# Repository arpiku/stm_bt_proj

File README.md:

# stm_bt_proj
A simple bluetoth PCB project based STM32 Microcontroller.

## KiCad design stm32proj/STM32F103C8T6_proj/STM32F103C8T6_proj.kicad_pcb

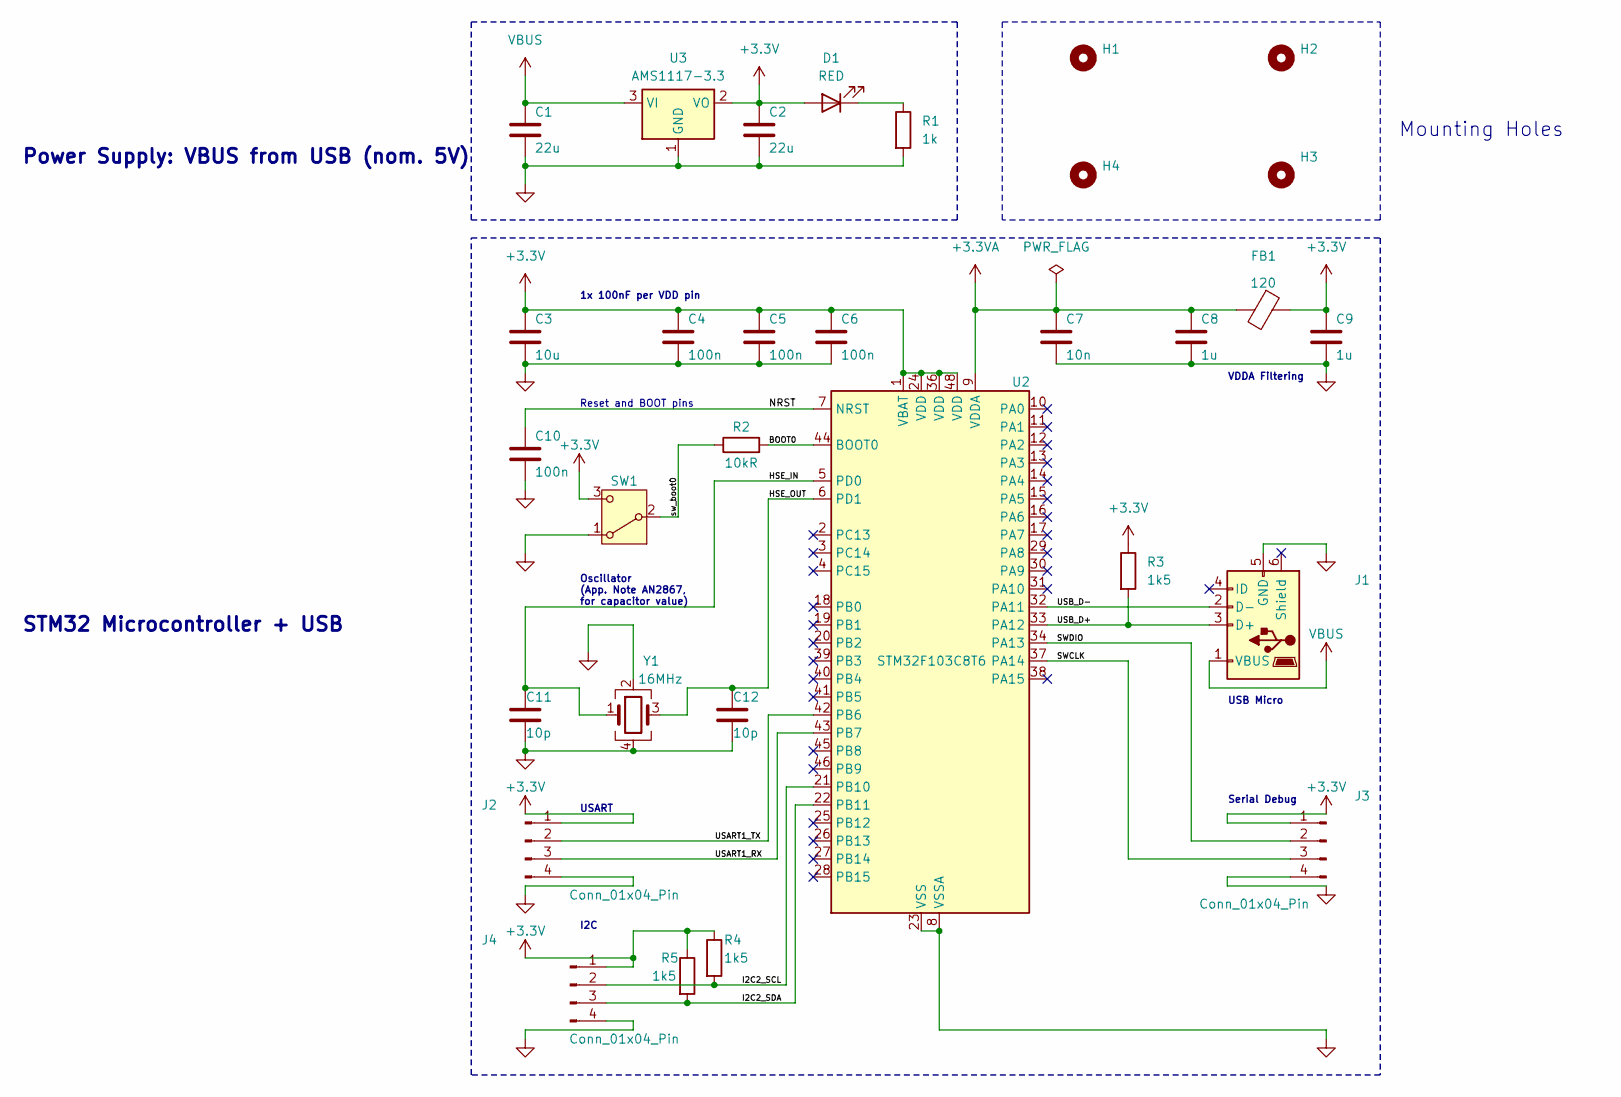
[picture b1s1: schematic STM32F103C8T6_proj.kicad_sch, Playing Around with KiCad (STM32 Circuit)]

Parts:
C1, C2: 22u; C_0805_2012Metric
C3: 10u; C_0805_2012Metric
C4, C5, C6, C10: 100n; C_0402_1005Metric
C7: 10n; C_0402_1005Metric
C8, C9: 1u; C_0402_1005Metric
C11, C12: 10p; C_0402_1005Metric
D1: RED; LED_0402_1005Metric
FB1: 120; L_0603_1608Metric
H1, H2, H3, H4: MountingHole; MountingHole_2.2mm_M2
J1: USB_B_Micro; USB_Micro-B_Wuerth_629105150521
J2, J3, J4: Conn_01x04_Pin; PinHeader_1x04_P1.27mm_Vertical
R1: 1k; R_0402_1005Metric
R2: 10kR; R_0402_1005Metric
R3, R4, R5: 1k5; R_0402_1005Metric
SW1: SW_SPDT; SW_SPDT_PCM12
U2: STM32F103C8T6; LQFP-48_7x7mm_P0.5mm
U3: AMS1117-3.3; SOT-223-3_TabPin2
Y1: 16MHz; Crystal_SMD_3225-4Pin_3.2x2.5mm

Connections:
+3.3V: C2.1, C3.1, C4.1, C5.1, C6.1, C9.1, D1.2 (A), FB1.1, J2.1, J3.1, J4.1, R3.1, R4.1, R5.1, SW1.3 (C), U2.1 (VBAT), U2.24 (VDD), U2.36 (VDD), U2.48 (VDD), U3.2 (VO); also elsewhere on the board
+3.3VA: C7.1, C8.1, FB1.2, U2.9 (VDDA)
/BOOT0: R2.2, U2.44 (BOOT0)
/HSE_IN: C11.1, U2.5 (PD0), Y1.1
/HSE_OUT: C12.1, U2.6 (PD1), Y1.3
/I2C2_SCL: J4.2, R4.2, U2.21 (PB10); also elsewhere on the board
/I2C2_SDA: J4.3, R5.2, U2.22 (PB11); also elsewhere on the board
/NRST: C10.1, U2.7 (NRST)
/SWCLK: J3.3, U2.37 (PA14); also elsewhere on the board
/SWDIO: J3.2, U2.34 (PA13); also elsewhere on the board
/USART1_RX: J2.3, U2.43 (PB7); also elsewhere on the board
/USART1_TX: J2.2, U2.42 (PB6); also elsewhere on the board
/USB_D+: J1.3 (D+), R3.2, U2.33 (PA12)
/USB_D-: J1.2 (D-), U2.32 (PA11)
/sw_boot0: R2.1, SW1.2 (B)
GND: C1.2, C2.2, C3.2, C4.2, C5.2, C6.2, C7.2, C8.2, C9.2, C10.2, C11.2, C12.2, J1.5 (GND), J2.4, J3.4, J4.4, R1.2, SW1.1 (A), U2.8 (VSSA), U2.23 (VSS), U2.35 (VSS), U2.47 (VSS), U3.1 (GND), Y1.2, Y1.4; also elsewhere on the board
unnamed: D1.1 (K), R1.1
VBUS: C1.1, J1.1 (VBUS), U3.3 (VI)

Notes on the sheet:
STM32 Microcontroller + USB
USART
Reset and BOOT pins
Oscillator (App. Note AN2867, for capacitor value)
Power Supply: VBUS from USB (nom. 5V)
I2C
USB Micro
VDDA Filtering
1x 100nF per VDD pin
Mounting Holes
Serial Debug

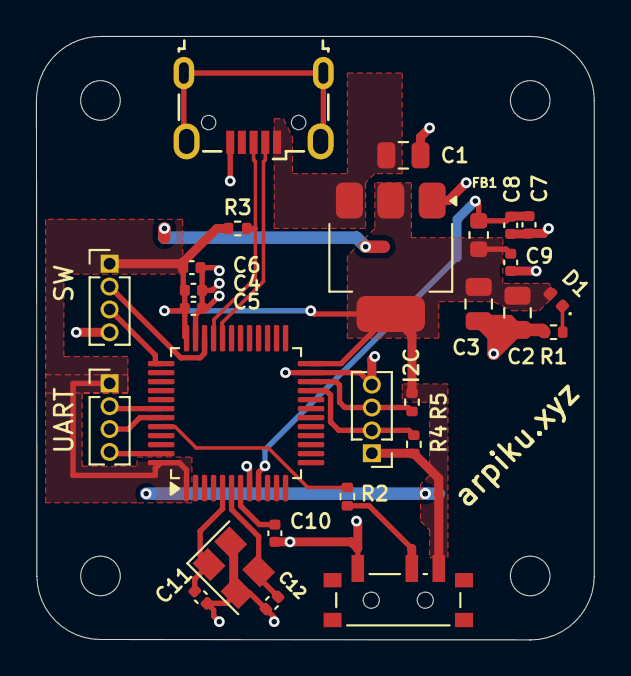
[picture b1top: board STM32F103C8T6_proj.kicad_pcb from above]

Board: 2 copper layers, 31.0 x 33.5 mm, 31 parts (0 on the bottom side), 18 nets.

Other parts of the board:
I2C: Conn_01x04_Pin; PinHeader_1x04_P1.27mm_Vertical
SW: Conn_01x04_Pin; PinHeader_1x04_P1.27mm_Vertical
UART: Conn_01x04_Pin; PinHeader_1x04_P1.27mm_Vertical

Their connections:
+3.3V: I2C.1, SW.1, UART.1; also elsewhere on the board
/I2C2_SCL: I2C.2; also elsewhere on the board
/I2C2_SDA: I2C.3; also elsewhere on the board
/SWCLK: SW.3; also elsewhere on the board
/SWDIO: SW.2; also elsewhere on the board
/USART1_RX: UART.3; also elsewhere on the board
/USART1_TX: UART.2; also elsewhere on the board
GND: I2C.4, SW.4, UART.4; also elsewhere on the board

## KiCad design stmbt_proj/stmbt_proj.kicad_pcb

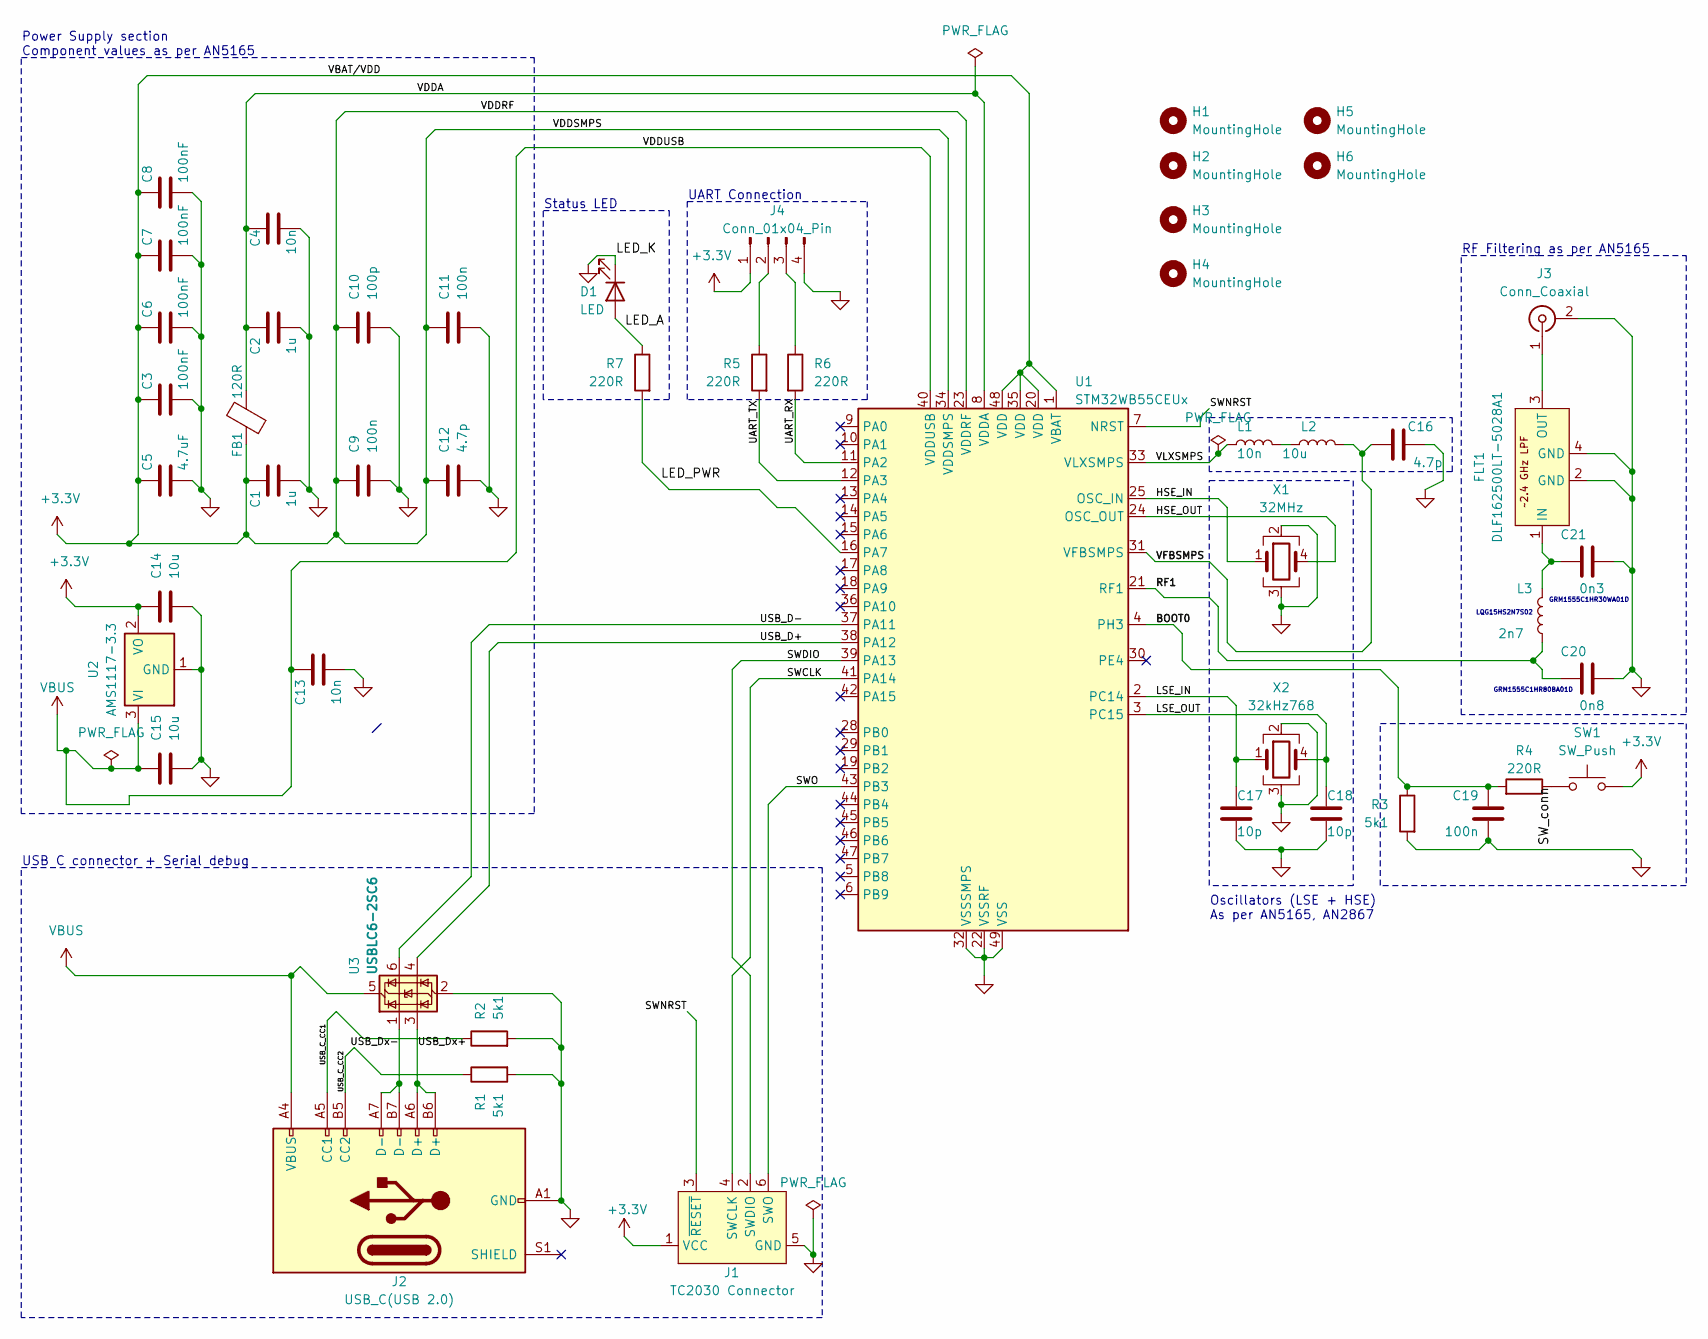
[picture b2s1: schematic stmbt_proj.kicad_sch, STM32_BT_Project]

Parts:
C1, C2: 1u; C_0603_1608Metric
C3, C6, C7, C8: 100nF; C_0402_1005Metric
C4: 10n; C_0402_1005Metric
C5: 4.7uF; C_0603_1608Metric
C9, C11: 100n; C_0402_1005Metric
C10: 100p; C_0402_1005Metric
C12, C16: 4.7p; C_0402_1005Metric
C13: 10n; C_0603_1608Metric
C14, C15: 10u; C_0603_1608Metric
C17, C18: 10p; C_0402_1005Metric
C19: 100n; C_0603_1608Metric
C20: 0n8; C_0402_1005Metric
C21: 0n3; C_0402_1005Metric
D1: LED; LED_0402_1005Metric
FB1: 120R; L_0402_1005Metric
FLT1: DLF162500LT-5028A1
H1, H2, H3, H4, H5, H6: MountingHole; MountingHole_2.2mm_M2_ISO7380_Pad
J1: TC2030 Connector; Tag-Connect_TC2030-IDC-FP_2x03_P1.27mm_Vertical
J2: USB_C(USB 2.0); USB_C_Receptacle_GCT_USB4105-xx-A_16P_TopMnt_Horizontal
J3: Conn_Coaxial; U.FL_Hirose_U.FL-R-SMT-1_Vertical
J4: Conn_01x04_Pin; JST_EH_S4B-EH_1x04_P2.50mm_Horizontal
L1: 10n; L_0402_1005Metric
L2: 10u; L_0603_1608Metric
L3: 2n7; L_0402_1005Metric
R1, R2, R3: 5k1; R_0603_1608Metric
R4, R5, R6, R7: 220R; R_0603_1608Metric
SW1: SW_Push; SW_PUSH_6mm_H4.3mm
U1: STM32WB55CEUx; QFN-48-1EP_7x7mm_P0.5mm_EP5.6x5.6mm
U2: AMS1117-3.3; SOT-223-3_TabPin2
U3: USBLC6-2SC6; SOT-23-6
X1: 32MHz; Crystal_SMD_2016-4Pin_2.0x1.6mm
X2: 32kHz768; Crystal_SMD_2016-4Pin_2.0x1.6mm

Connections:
+3.3V: C1.1, C3.1, C5.1, C6.1, C7.1, C8.1, C9.1, C10.1, C11.1, C12.1, C14.1, FB1.1, J1.1 (VCC), J4.1, SW1.2, U1.1 (VBAT), U1.20 (VDD), U1.23 (VDDRF), U1.34 (VDDSMPS), U1.35 (VDD), U1.48 (VDD), U2.2 (VO)
/BOOT0: C19.1, R3.1, R4.2, U1.4 (PH3)
/HSE_IN: U1.25 (OSC_IN), X1.1
/HSE_OUT: U1.24 (OSC_OUT), X1.4
/LED_A: D1.2 (A), R7.1; also elsewhere on the board
/LED_PWR: R7.2, U1.16 (PA7)
/LSE_IN: C17.1, U1.2 (PC14), X2.1
/LSE_OUT: C18.1, U1.3 (PC15), X2.4
/RF1: C20.1, L3.1, U1.21 (RF1)
/SWCLK: J1.4 (SWCLK), U1.41 (PA14)
/SWDIO: J1.2 (SWDIO), U1.39 (PA13)
/SWNRST: J1.3 (~RESET), U1.7 (NRST)
/SWO: J1.6 (SWO), U1.43 (PB3)
/SW_conn: R4.1, SW1.1
/UART_RX: R6.2, U1.11 (PA2)
/UART_TX: R5.2, U1.12 (PA3)
/USB_C_CC1: J2.A5 (CC1), R2.1
/USB_C_CC2: J2.B5 (CC2), R1.1
/USB_D+: U1.38 (PA12), U3.4 (I/O2)
/USB_D-: U1.37 (PA11), U3.6 (I/O1)
/USB_Dx+: J2.A6 (D+), J2.B6 (D+), U3.3 (I/O2)
/USB_Dx-: J2.A7 (D-), J2.B7 (D-), U3.1 (I/O1)
/VDDA: C2.1, C4.1, FB1.2, U1.8 (VDDA)
/VFBSMPS: C16.1, L2.2, U1.31 (VFBSMPS)
/VLXSMPS: L1.2, U1.33 (VLXSMPS)
GND: C1.2, C2.2, C3.2, C4.2, C5.2, C6.2, C7.2, C8.2, C9.2, C10.2, C11.2, C12.2, C13.2, C14.2, C15.2, C16.2, C17.2, C18.2, C19.2, C20.2, C21.2, D1.1 (K), FLT1.2 (GND), FLT1.4 (GND), J1.5 (GND), J2.A1 (GND), J2.A12 (GND), J2.B1 (GND), J2.B12 (GND), J3.2 (Ext), J4.4, R1.2, R2.2, R3.2, U1.22 (VSSRF), U1.32 (VSSSMPS), U1.49 (VSS), U2.1 (GND), U3.2 (GND), X1.2, X1.3, X2.2, X2.3; also elsewhere on the board
unnamed: C21.1, FLT1.1 (IN), L3.2
unnamed: FLT1.3 (OUT), J3.1 (In)
unnamed: J4.2, R5.1
unnamed: J4.3, R6.1
unnamed: L1.1, L2.1
VBUS: C13.1, C15.1, J2.A4 (VBUS), J2.A9 (VBUS), J2.B4 (VBUS), J2.B9 (VBUS), U1.40 (VDDUSB), U2.3 (VI), U3.5 (VBUS)

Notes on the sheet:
LQG15HS2N7S02
Oscillators (LSE + HSE) As per AN5165, AN2867
USB C connector + Serial debug
RF Filtering as per AN5165
GRM1555C1HR80BA01D
UART Connection
GRM1555C1HR30WA01D
Power Supply section Component values as per AN5165
Status LED

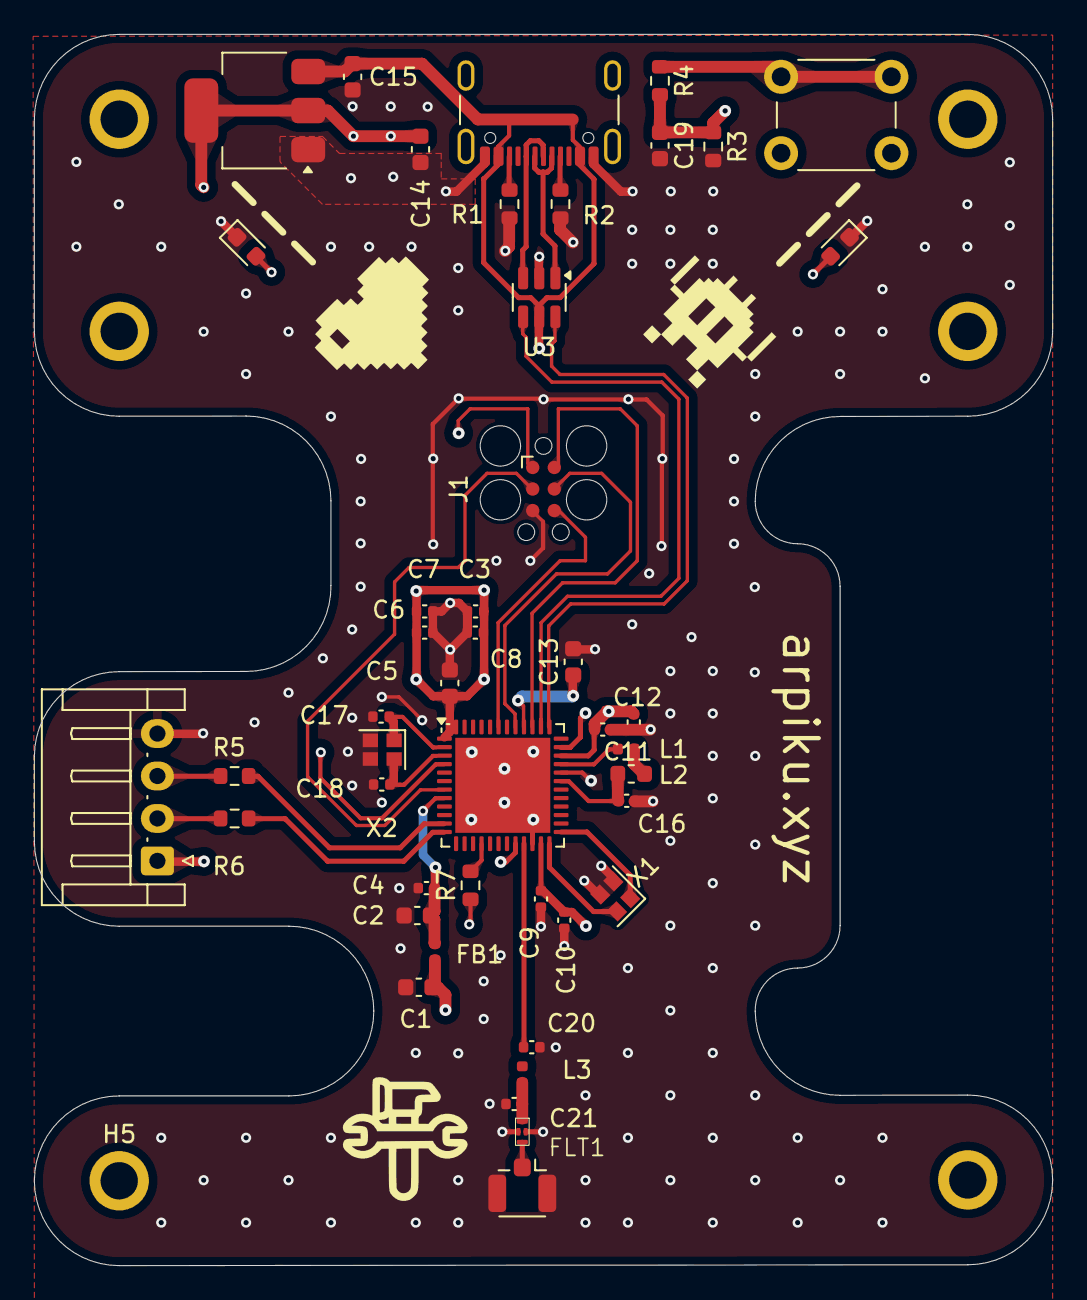
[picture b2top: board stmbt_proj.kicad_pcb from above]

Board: 4 copper layers, 60.0 x 72.5 mm, 51 parts (0 on the bottom side), 32 nets.

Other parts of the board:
---: LED; LED_0603_1608Metric
---#2: LED; LED_0603_1608Metric

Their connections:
/LED_A: ---.2 (A), ---#2.2 (A); also elsewhere on the board
GND: ---.1 (K), ---#2.1 (K); also elsewhere on the board

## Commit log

2024-10-25 files
